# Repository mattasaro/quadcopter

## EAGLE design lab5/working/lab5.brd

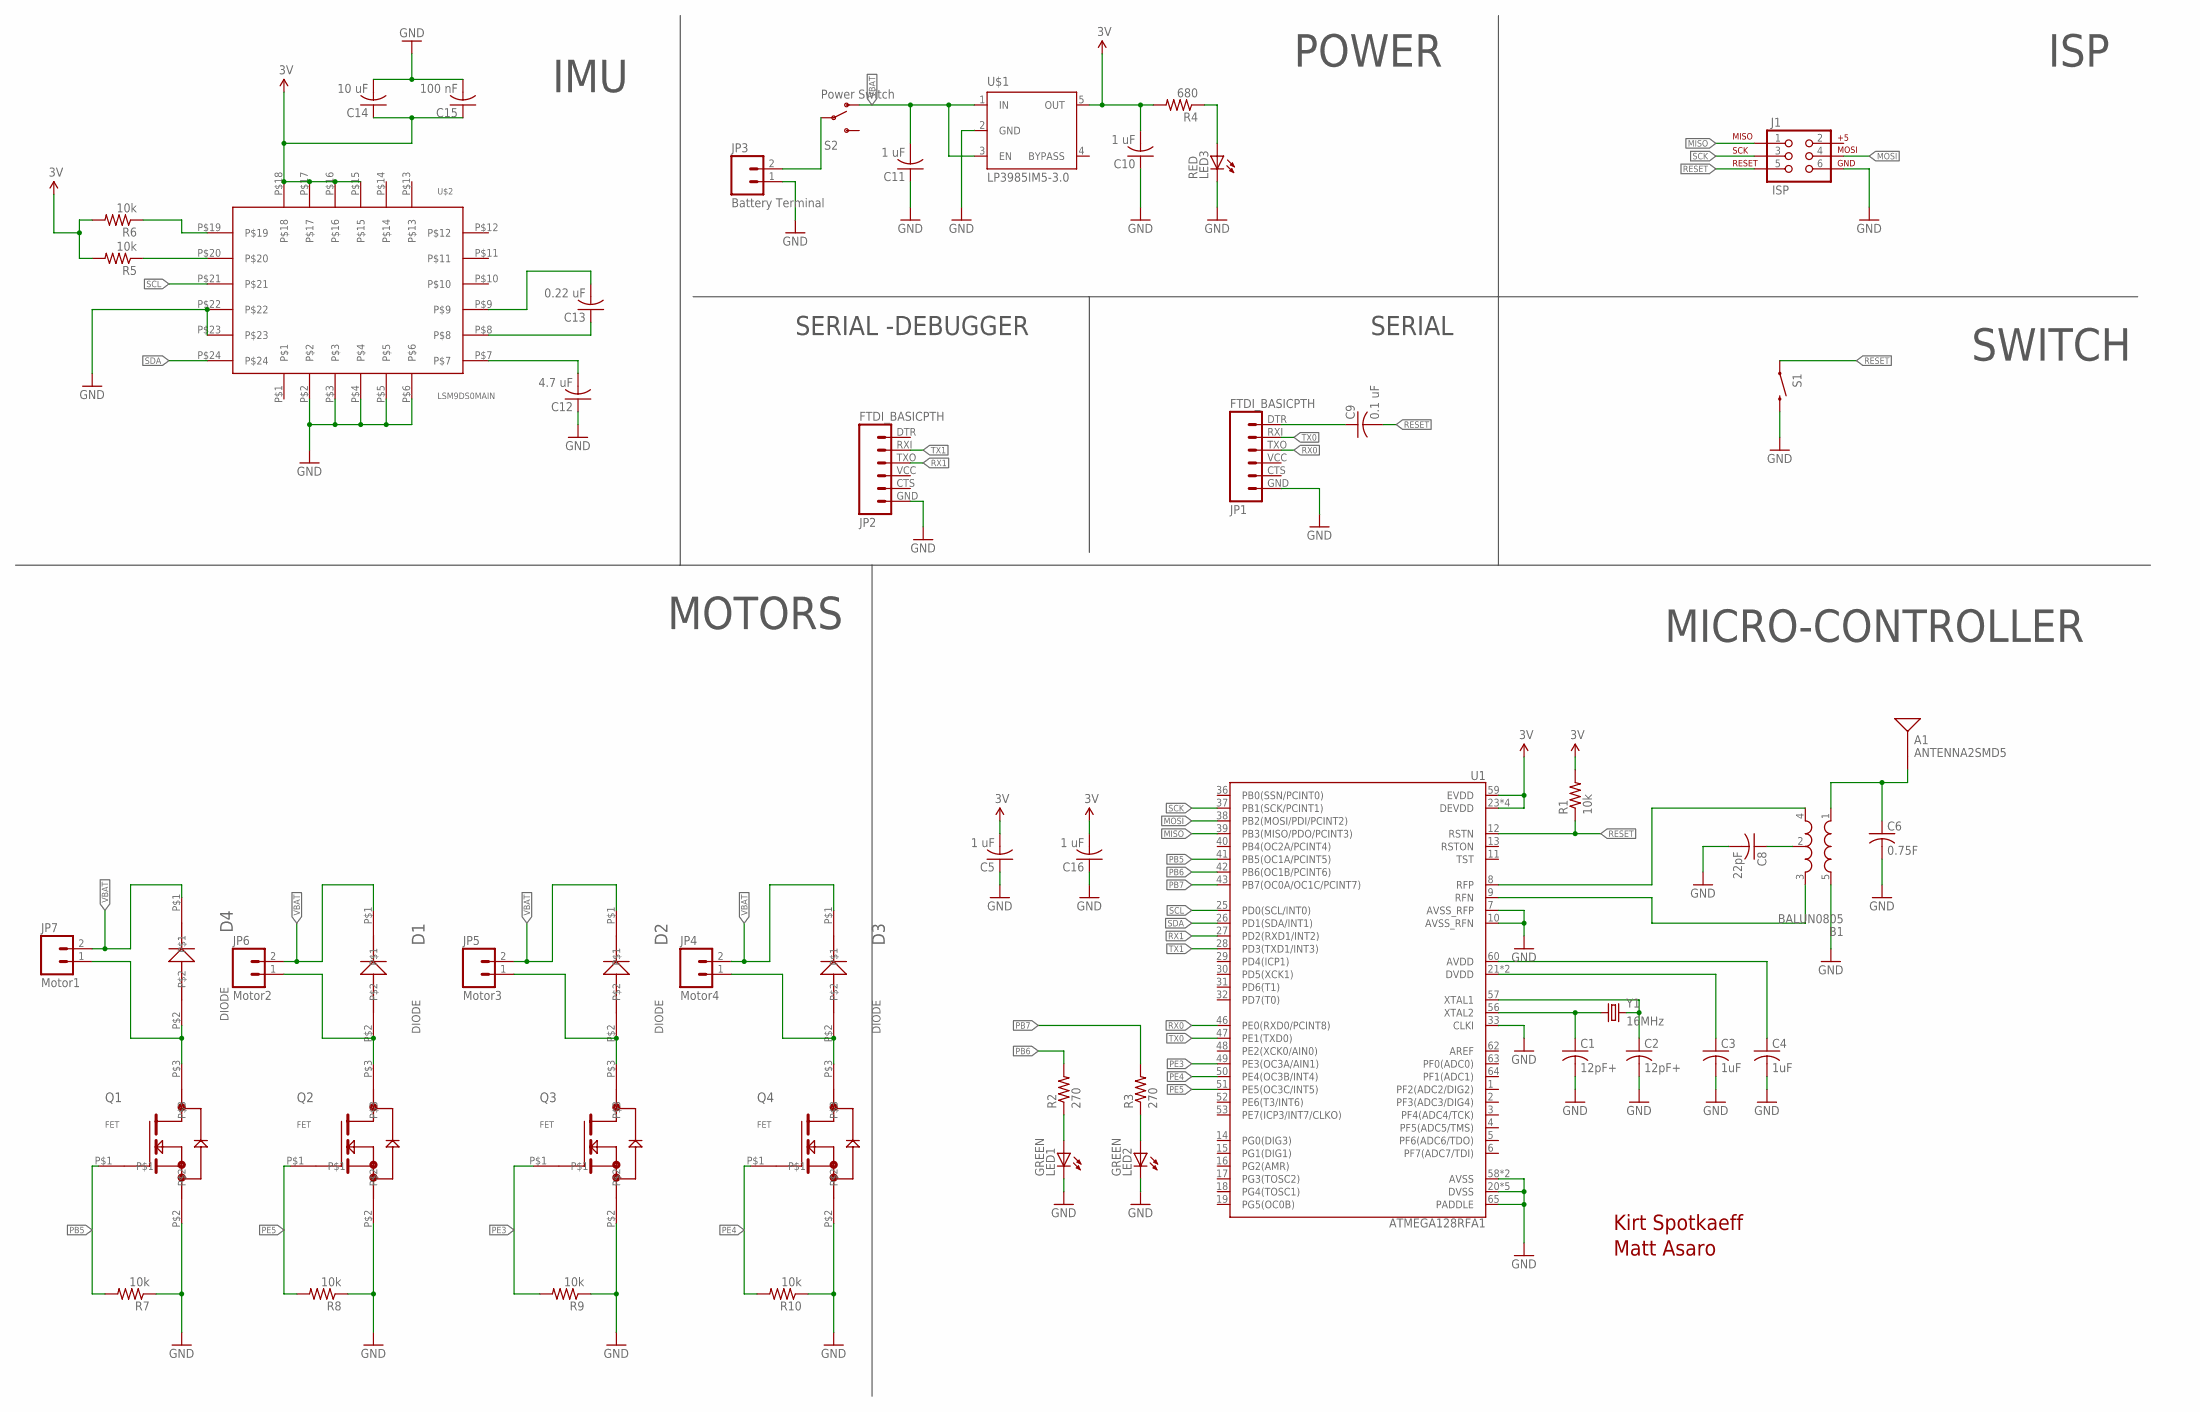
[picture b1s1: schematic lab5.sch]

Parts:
A1: ANTENNA2SMD5; ANTENNA-CHIP5
B1: BALUN0805; BALUN
C1, C2: 12pF+; C0805
C3, C4: 1uF; C0805
C5, C10, C11, C16: 1 uF; C0805
C6: 0.75F; C0805
C8: 22pF; C0805
C9: 0.1 uF; C0805
C12: 4.7 uF; C0805
C13: 0.22 uF; C0805
C14: 10 uF; C0805
C15: 100 nF; C0805
D1, D2, D3, D4: DIODE
J1: ISP; 2X3-NS
JP1, JP2: FTDI_BASICPTH; FTDI_BASIC
JP3: Battery Terminal; 1X02
JP4: Motor4; 1X02
JP5: Motor3; 1X02
JP6: Motor2; 1X02
JP7: Motor1; 1X02
LED1, LED2: GREEN; CHIP-LED0805
LED3: RED; CHIP-LED0805
Q1, Q2, Q3, Q4: FET
R1, R5, R6, R7, R8, R9, R10: 10k; R0805
R2, R3: 270; R0805
R4: 680; R0805
S1: SWITCH-MOMENTARY-2SMD; TACTILE_SWITCH_SMD
S2: Power Switch; SWITCH-SPDT
U1: ATMEGA128RFA1; QFN-64
U$1: LP3985IM5-3.0; SOT23-DBV
U$2: LSM9DS0MAIN; LSM9DS0
Y1: 16MHz; CRYSTAL-SMD-5X3

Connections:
3.3V: C5.2, C10.2, C14.1, C15.1, C16.2, R1.2, R4.2, R5.2, R6.2, U1.23 (DEVDD), U1.34 (DEVDD), U1.44 (DEVDD), U1.54 (DEVDD), U1.59 (EVDD), U$1.5 (OUT), U$2.P$15, U$2.P$16, U$2.P$17, U$2.P$18
GND: B1.5 (GND), C1.2, C2.2, C3.2, C4.2, C5.1, C6.2, C8.2, C10.1, C11.1, C12.1, C14.2, C15.2, C16.1, J1.6, JP1.GND (6), JP2.GND (6), JP3.1, LED1.C, LED2.C, LED3.C, Q1.P$2, Q2.P$2, Q3.P$2, Q4.P$2, R7.1, R8.1, R9.1, R10.1, S1.3 (2), U1.7 (AVSS_RFP), U1.10 (AVSS_RFN), U1.20 (DVSS), U1.24 (DVSS), U1.33 (CLKI), U1.35 (DVSS), U1.45 (DVSS), U1.55 (DVSS), U1.58 (AVSS), U1.61 (AVSS), U1.65 (PADDLE), U$1.2 (GND), U$2.P$2, U$2.P$3, U$2.P$4, U$2.P$5, U$2.P$6, U$2.P$22, U$2.P$23
MISO: J1.1, U1.39 (PB3(MISO/PDO/PCINT3))
MOSI: J1.4, U1.38 (PB2(MOSI/PDI/PCINT2))
unnamed: C1.1, U1.56 (XTAL2), Y1.1
unnamed: B1.2 (GND), C8.1
unnamed: D1.P$2, JP6.1, Q2.P$3
unnamed: A1.FEED, B1.1 (IN), C6.1
unnamed: LED3.A, R4.1
unnamed: JP3.2, S2.2
unnamed: LED1.A, R2.1
unnamed: LED2.A, R3.1
unnamed: C9.1, JP1.DTR (1)
unnamed: C2.1, U1.57 (XTAL1), Y1.3 (2)
unnamed: D3.P$2, JP4.1, Q4.P$3
unnamed: C3.1, U1.21 (DVDD), U1.22 (DVDD)
unnamed: C4.1, U1.60 (AVDD)
unnamed: D2.P$2, JP5.1, Q3.P$3
unnamed: D4.P$2, JP7.1, Q1.P$3
unnamed: B1.3 (OUT2), U1.9 (RFN)
unnamed: B1.4 (OUT1), U1.8 (RFP)
unnamed: C12.2, U$2.P$7
unnamed: C13.2, U$2.P$9
unnamed: C13.1, U$2.P$8
unnamed: R5.1, U$2.P$20
unnamed: R6.1, U$2.P$19
PB5: Q1.P$1, R7.2, U1.41 (PB5(OC1A/PCINT5))
PB6: R2.2, U1.42 (PB6(OC1B/PCINT6))
PB7: R3.2, U1.43 (PB7(OC0A/OC1C/PCINT7))
PE3: Q3.P$1, R9.2, U1.49 (PE3(OC3A/AIN1))
PE4: Q4.P$1, R10.2, U1.50 (PE4(OC3B/INT4))
PE5: Q2.P$1, R8.2, U1.51 (PE5(OC3C/INT5))
RESET: C9.2, J1.5, R1.1, S1.1, U1.12 (RSTN)
RX0: JP1.TXO (3), U1.46 (PE0(RXD0/PCINT8))
RX1: JP2.TXO (3), U1.27 (PD2(RXD1/INT2))
SCK: J1.3, U1.37 (PB1(SCK/PCINT1))
SCL: U1.25 (PD0(SCL/INT0)), U$2.P$21
SDA: U1.26 (PD1(SDA/INT1)), U$2.P$24
TX0: JP1.RXI (2), U1.47 (PE1(TXD0))
TX1: JP2.RXI (2), U1.28 (PD3(TXD1/INT3))
VBAT: C11.2, D1.P$1, D2.P$1, D3.P$1, D4.P$1, JP4.2, JP5.2, JP6.2, JP7.2, S2.1 (O), U$1.1 (IN), U$1.3 (EN)

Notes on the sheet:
Kirt Spotkaeff
Matt Asaro
IMU
MOTORS
MICRO-CONTROLLER
SWITCH
POWER
ISP
SERIAL -DEBUGGER
SERIAL

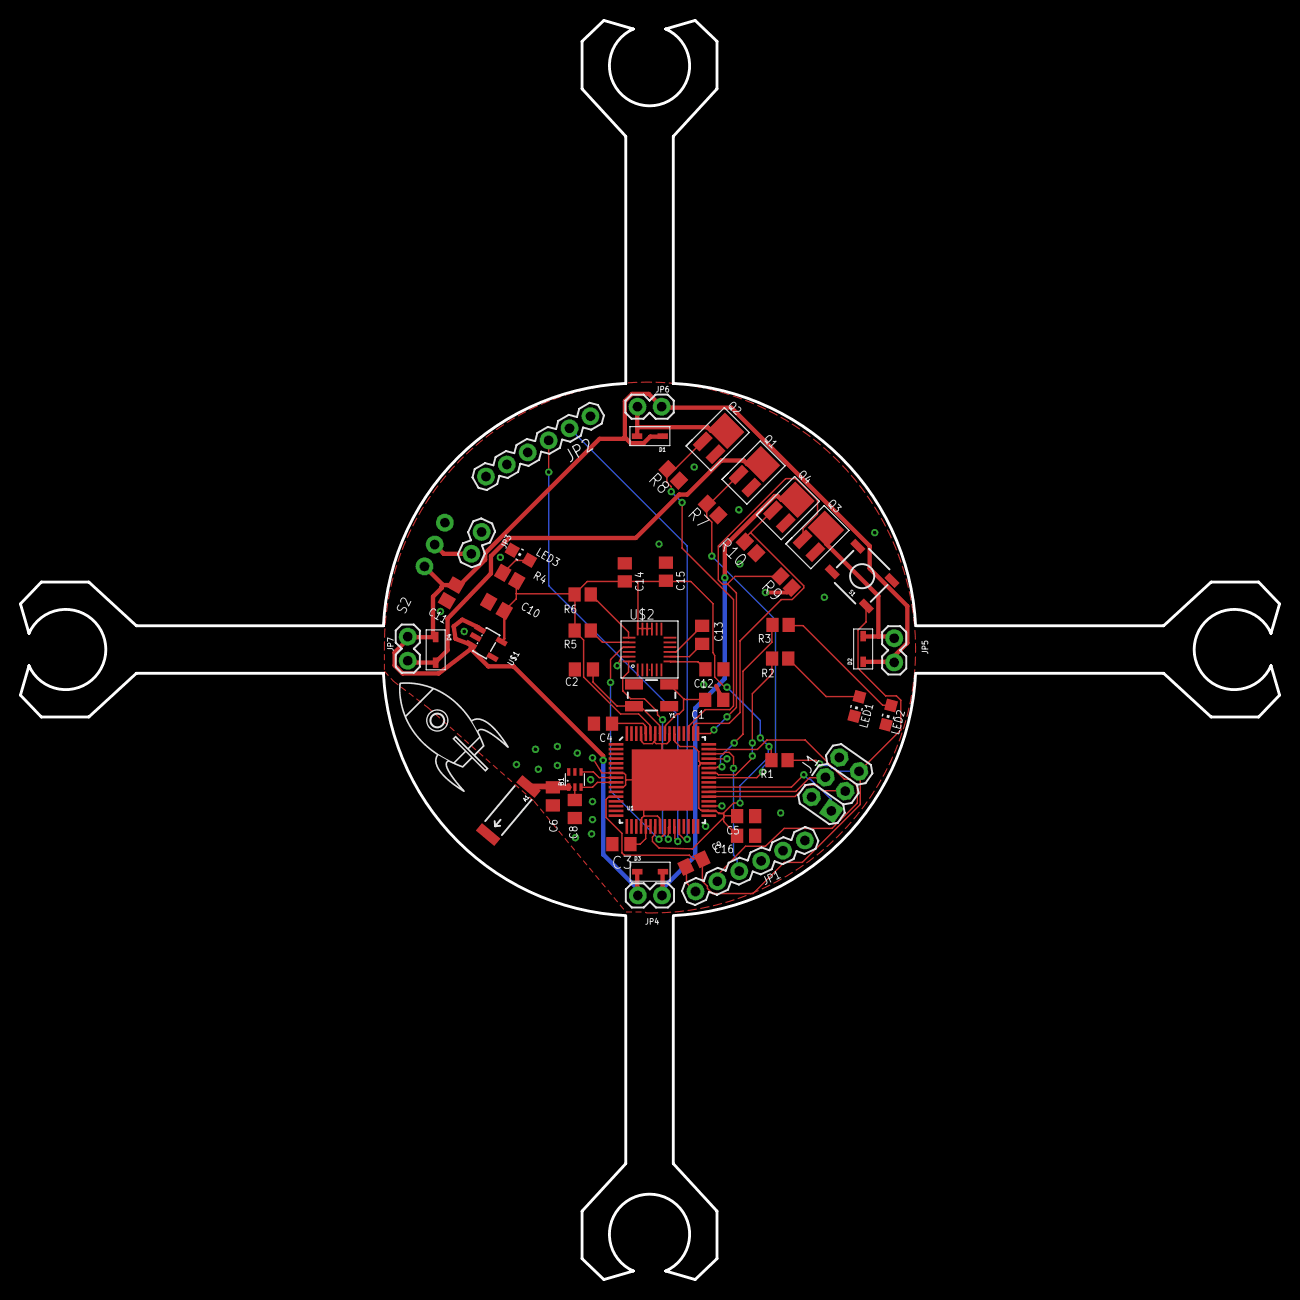
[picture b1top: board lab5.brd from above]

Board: 2 copper layers, 132.5 x 132.5 mm, 53 parts (0 on the bottom side), 41 nets.

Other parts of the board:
U$3: ROCKET_LOGO

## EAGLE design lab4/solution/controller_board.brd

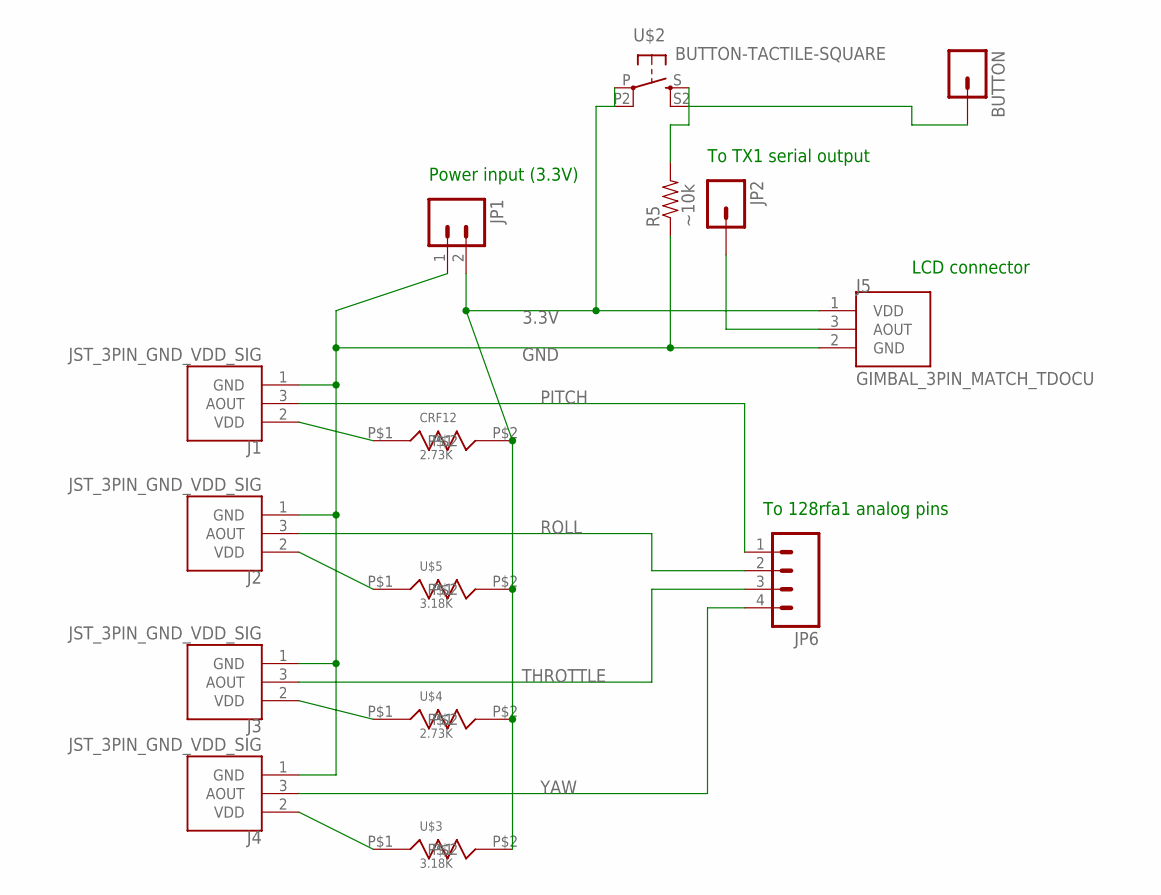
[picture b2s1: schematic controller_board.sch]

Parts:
BUTTON: M01PTH; 1X01
CRF12: 2.73K; CFR12
J1, J2, J3, J4: JST_3PIN_GND_VDD_SIG; JST-3-PTH-REVERSE
J5: GIMBAL_3PIN_MATCH_TDOCU; JST-3-PTH
JP1: M021X02_NO_SILK; 1X02_NO_SILK
JP2: M01PTH; 1X01
JP6: M04PTH; 1X04
R5: ~10k; AXIAL-0.4
U$2: BUTTON-TACTILE-SQUARE; BUTTON-TACTILE-SQUARE-ADAFRUIT1010
U$3, U$5: 3.18K; CFR12
U$4: 2.73K; CFR12

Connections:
3.3V: CRF12.P$2, J5.1 (VDD), JP1.2, U$2.P, U$2.P2 (P1), U$3.P$2, U$4.P$2, U$5.P$2
GND: J1.1 (GND), J2.1 (GND), J3.1 (GND), J4.1 (GND), J5.2 (GND), JP1.1, R5.P$1 (1)
unnamed: J4.2 (VDD), U$3.P$1
unnamed: J3.2 (VDD), U$4.P$1
unnamed: CRF12.P$1, J1.2 (VDD)
unnamed: J2.2 (VDD), U$5.P$1
unnamed: BUTTON.1, R5.P$2 (2), U$2.S, U$2.S2 (S1)
unnamed: J5.3 (AOUT), JP2.1
PITCH: J1.3 (AOUT), JP6.1
ROLL: J2.3 (AOUT), JP6.2
THROTTLE: J3.3 (AOUT), JP6.3
YAW: J4.3 (AOUT), JP6.4

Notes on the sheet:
To 128rfa1 analog pins
LCD connector
Power input (3.3V)
To TX1 serial output

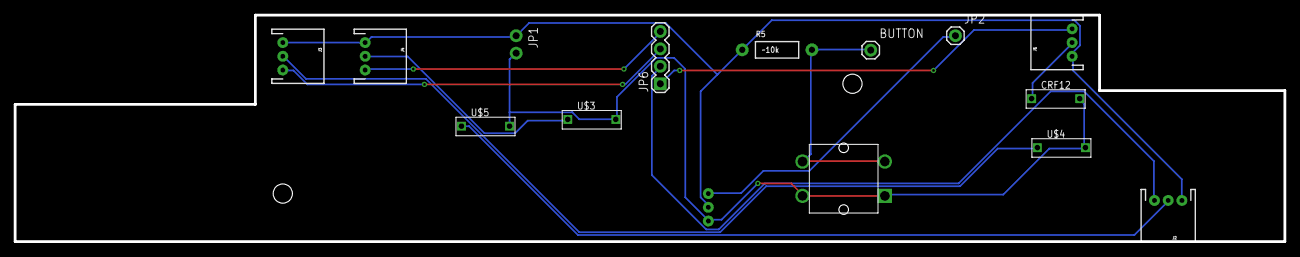
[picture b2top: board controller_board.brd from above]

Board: 2 copper layers, 185.0 x 33.0 mm, 16 parts (1 on the bottom side), 12 nets.

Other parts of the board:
U$1: CONNECTOR_BOARD_OUTLINE

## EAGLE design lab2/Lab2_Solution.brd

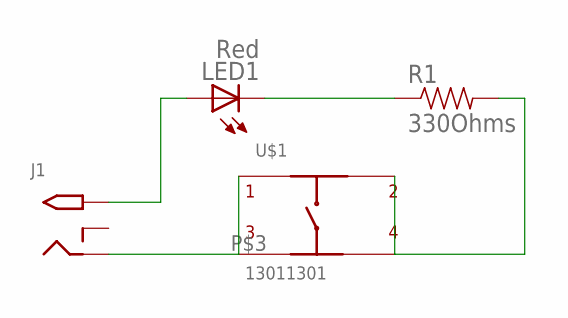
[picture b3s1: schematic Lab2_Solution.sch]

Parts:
J1: 2.1MMJACKTHM; PJ-102A
LED1: Red; LED5MM
R1: 330Ohms; AXIAL-0.3
U$1: 13011301; LSH.1301.9315

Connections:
unnamed: LED1.K (C), R1.P$1 (1)
unnamed: R1.P$2 (2), U$1.P$2 (2), U$1.P$4 (4)
unnamed: J1.RING, U$1.P$1 (1), U$1.P$3 (3)
unnamed: J1.TIP, LED1.A

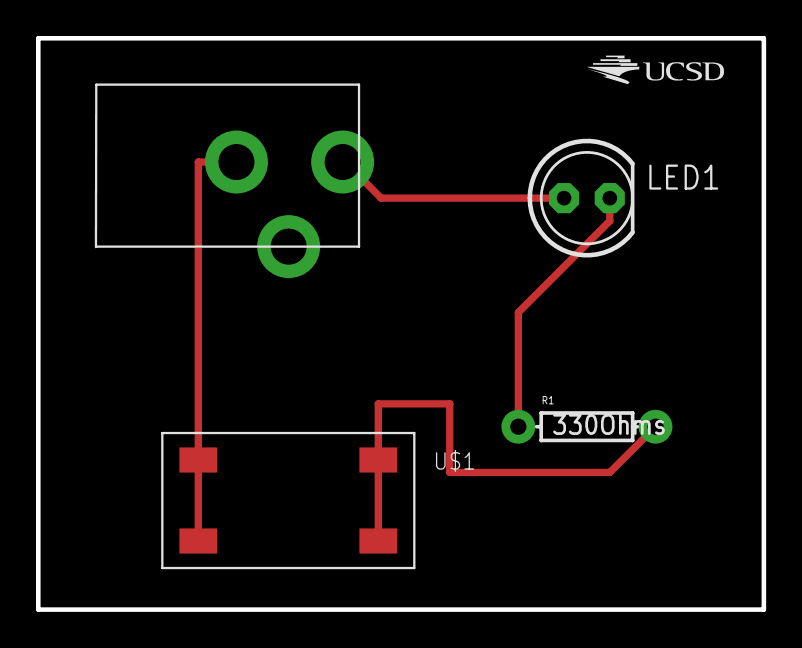
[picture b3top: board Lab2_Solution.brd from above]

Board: 2 copper layers, 40.3 x 31.7 mm, 5 parts (0 on the bottom side), 4 nets.

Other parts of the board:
U$2: UCSD_LOGO

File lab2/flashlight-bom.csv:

"Qty","Value","Device","Package","Parts","Description","",
"1","2.1MMJACKTHM","2.1MMJACKTHM","PJ-102A","J1","2.1mm x 5.5mm THM DC jack with internal switch. Digikey part #PJ-102A, 4UCON part #05537","",
"1","330Ohms","RESISTORAXIAL-0.3","AXIAL-0.3","R1","Resistor","",
"1","BUTTON-TACTILE-SQUARE","BUTTON-TACTILE-SQUARE","BUTTON-TACTILE-SQUARE-ADAFRUIT1010","S1","","",
"1","Red","LED5MM","LED5MM","LED1","LED","",

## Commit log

2015-04-09 Correct grid for Button.
2015-04-10 finished lab 2
2015-04-10 finished
2015-04-17 initial commit for lab4
2015-04-17 pushing finished solution
2015-04-18 added lab5 folder
2015-04-18 schematic checkpoint
2015-04-18 updated lab5.sch
2015-04-21 added power connectors
2015-04-21 added power IMU
2015-04-21 finished lab5
2015-04-21 added document info in frame
2015-04-23 fixed some ERC errors
2015-04-23 updated schematic to look nice
2015-04-23 updated green led resistor values to 300
2015-04-25 added Kirt's library
2015-04-28 changed FET board
2015-04-28 FIXED FET FOR REAL THIS TIME
2015-04-28 updated schematic to use Kirt library
2015-04-28 grounded CLKI on microcontroller
2015-04-28 added 2nd cap
2015-04-30 fixed resistor values according to piazza post from Jorge and schematic review feedback
2015-04-30 first pass at board layout
2015-05-01 made board circular
2015-05-02 added motor arms but still need to be aligned precisely
2015-05-05 Added ground planes and rotated
2015-05-05 added radio circuit
2015-05-05 first pass at logo in lab4.lbr
2015-05-05 fixed radio
2015-05-05 added logo to board
2015-05-05 updated radio, moved antenna closer
2015-05-05 fixed board outline
2015-05-08 finished everything hopefully
2015-05-08 foxed clearance/ notation issues
2015-05-08 added cam files
2015-05-12 edited some things from design review
2015-05-12 redid cam files
2015-05-12 added zip file cam files
2015-05-12 added second dimension thing
2015-05-12 edited logo orientation
2015-05-12 fixed some problems from prof
2015-05-12 fixed swanson errors
2015-05-17 added BOM

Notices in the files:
parts and their libraries:
SparkFun-Connectors: Licensing: Creative Commons ShareAlike 4.0 International - https://creativecommons.org/licenses/by-sa/4.0
